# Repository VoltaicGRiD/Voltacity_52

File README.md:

## Voltacity

A custom designed, split ergonomic keyboard with 52 keys, designed for personal use. This repository contains the KiCAD files for the baseboard of the keyboard.

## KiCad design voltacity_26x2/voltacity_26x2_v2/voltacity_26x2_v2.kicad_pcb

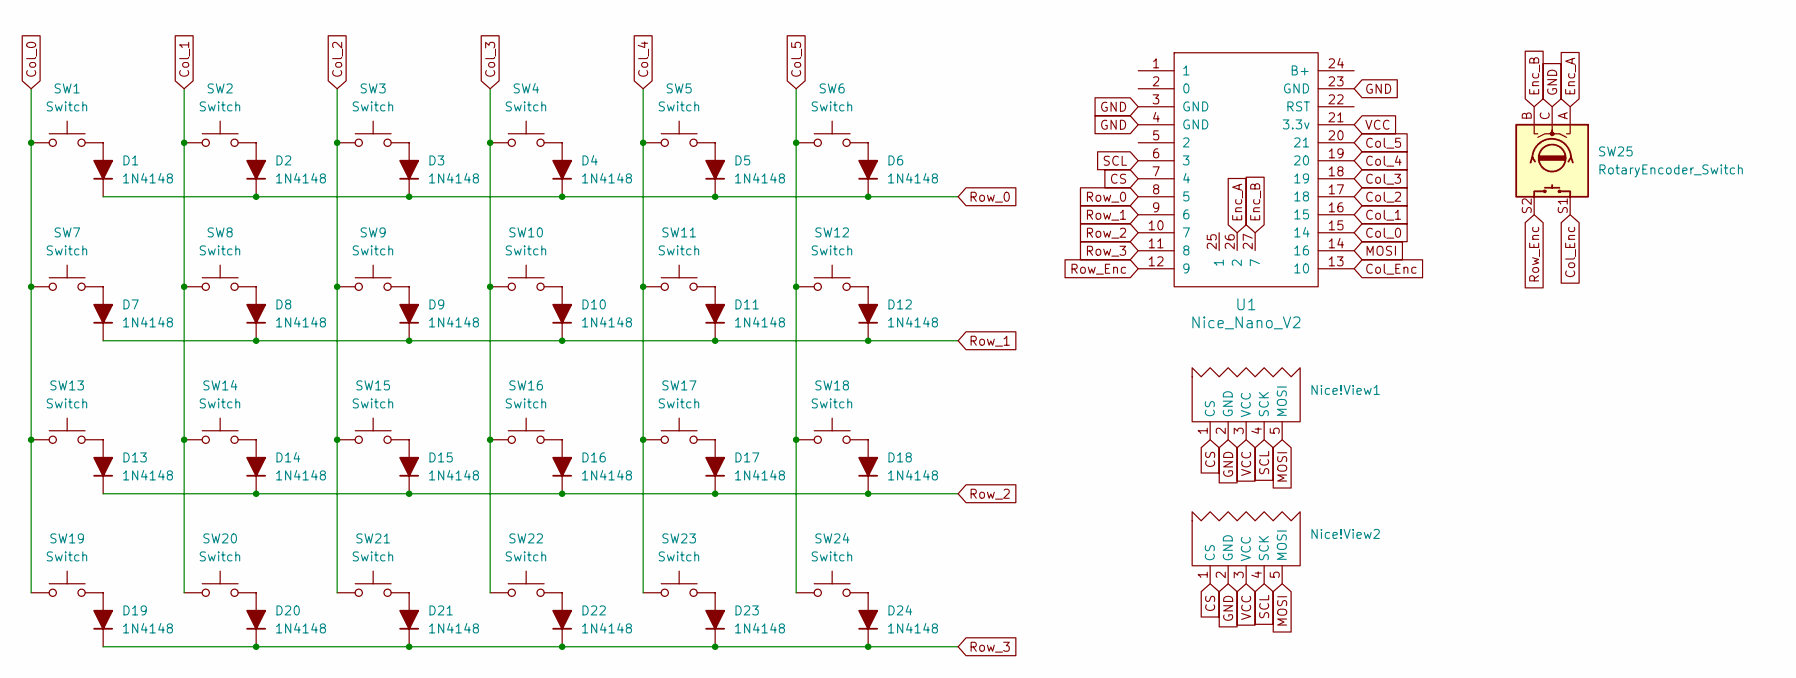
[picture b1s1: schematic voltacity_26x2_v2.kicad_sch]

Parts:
D1, D2, D3, D4, D5, D6, D7, D8, D9, D10, D11, D12, D13, D14, D15, D16, D17, D18, D19, D20, D21, D22, D23, D24: 1N4148; SOD123_DIO
Nice!View1, Nice!View2: Nice!View
SW1, SW2, SW3, SW4, SW5, SW6, SW7, SW8, SW9, SW10, SW11, SW12, SW13, SW14, SW15, SW16, SW17, SW18, SW19, SW20, SW21, SW22, SW23, SW24: Switch; SW_choc_Reversible_1u
SW25: RotaryEncoder_Switch; RotaryEncoder_Alps_EC11E-Switch_Vertical_H20mm_CircularMoun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
U1: Nice_Nano_V2

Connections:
CS: Nice!View1.1 (CS), Nice!View2.1 (CS), U1.7 (4); also elsewhere on the board
Col_0: SW1.1, SW7.1, SW13.1, SW19.1, U1.15 (14)
Col_1: SW2.1, SW8.1, SW14.1, SW20.1, U1.16 (15)
Col_2: SW3.1, SW9.1, SW15.1, SW21.1, U1.17 (18)
Col_3: SW4.1, SW10.1, SW16.1, SW22.1, U1.18 (19)
Col_4: SW5.1, SW11.1, SW17.1, SW23.1, U1.19 (20)
Col_5: SW6.1, SW12.1, SW18.1, SW24.1, U1.20 (21)
Col_Enc: SW25.S1, U1.13 (10)
Enc_A: SW25.A, U1.26 (2)
Enc_B: SW25.B, U1.27 (7)
GND: Nice!View1.2 (GND), Nice!View2.2 (GND), SW25.C, U1.3 (GND), U1.4 (GND), U1.23 (GND); also elsewhere on the board
MOSI: Nice!View1.5 (MOSI), Nice!View2.5 (MOSI), U1.14 (16); also elsewhere on the board
unnamed: D1.2 (A), SW1.2
unnamed: D2.2 (A), SW2.2
unnamed: D3.2 (A), SW3.2
unnamed: D4.2 (A), SW4.2
unnamed: D5.2 (A), SW5.2
unnamed: D6.2 (A), SW6.2
unnamed: D7.2 (A), SW7.2
unnamed: D8.2 (A), SW8.2
unnamed: D9.2 (A), SW9.2
unnamed: D10.2 (A), SW10.2
unnamed: D11.2 (A), SW11.2
unnamed: D12.2 (A), SW12.2
unnamed: D13.2 (A), SW13.2
unnamed: D14.2 (A), SW14.2
unnamed: D15.2 (A), SW15.2
unnamed: D16.2 (A), SW16.2
unnamed: D17.2 (A), SW17.2
unnamed: D18.2 (A), SW18.2
unnamed: D19.2 (A), SW19.2
unnamed: D20.2 (A), SW20.2
unnamed: D21.2 (A), SW21.2
unnamed: D22.2 (A), SW22.2
unnamed: D23.2 (A), SW23.2
unnamed: D24.2 (A), SW24.2
Row_0: D1.1 (K), D2.1 (K), D3.1 (K), D4.1 (K), D5.1 (K), D6.1 (K), U1.8 (5)
Row_1: D7.1 (K), D8.1 (K), D9.1 (K), D10.1 (K), D11.1 (K), D12.1 (K), U1.9 (6)
Row_2: D13.1 (K), D14.1 (K), D15.1 (K), D16.1 (K), D17.1 (K), D18.1 (K), U1.10 (7)
Row_3: D19.1 (K), D20.1 (K), D21.1 (K), D22.1 (K), D23.1 (K), D24.1 (K), U1.11 (8)
Row_Enc: SW25.S2, U1.12 (9)
SCL: Nice!View1.4 (SCK), Nice!View2.4 (SCK), U1.6 (3); also elsewhere on the board
VCC: Nice!View1.3 (VCC), Nice!View2.3 (VCC), U1.21 (3.3v); also elsewhere on the board

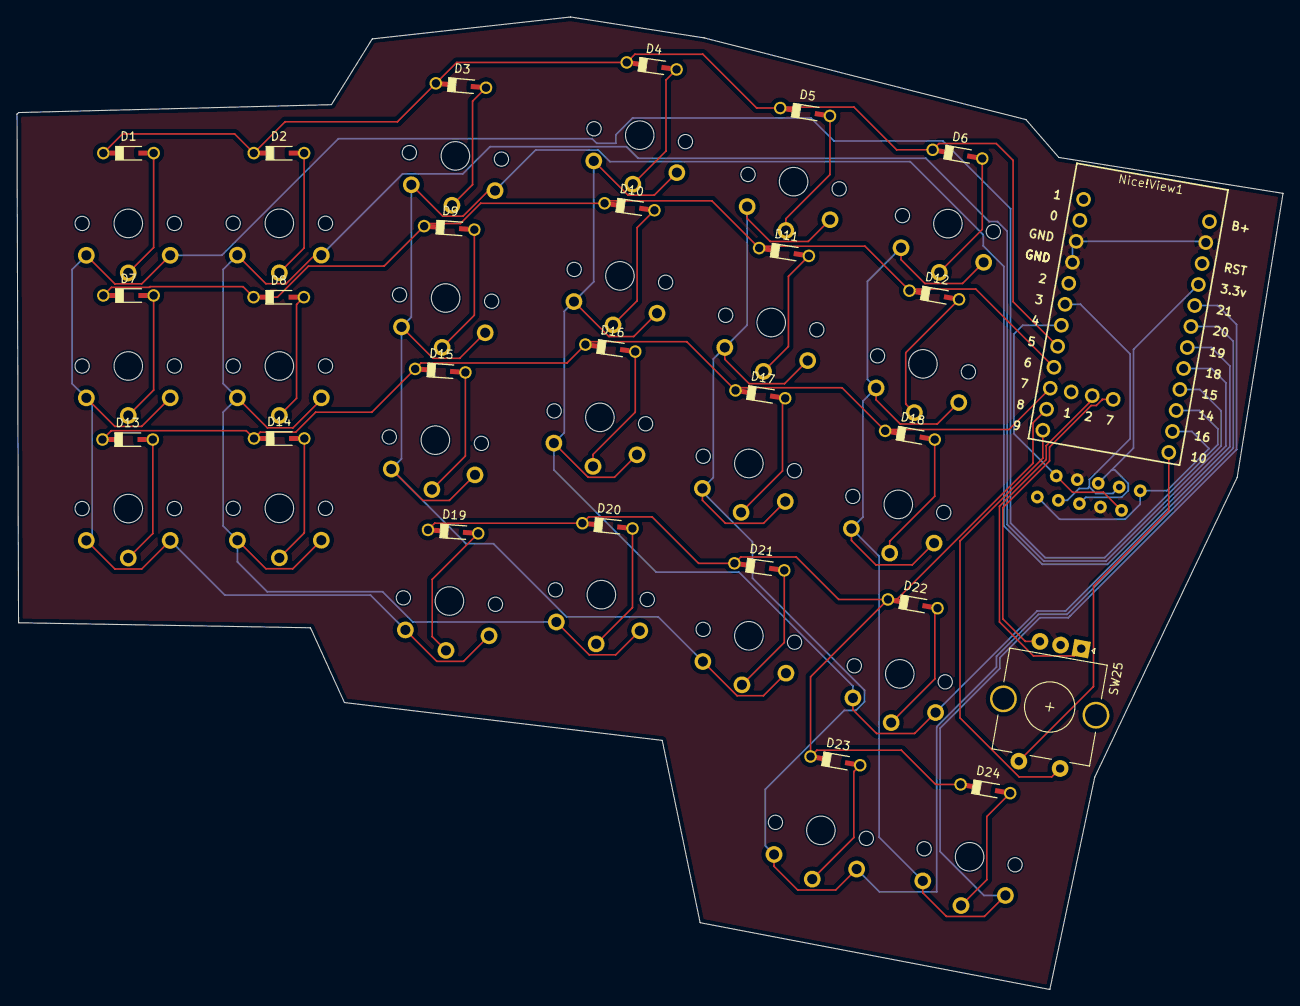
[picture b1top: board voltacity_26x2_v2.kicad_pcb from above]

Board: 2 copper layers, 150.9 x 115.9 mm, 52 parts (1 on the bottom side), 43 nets.

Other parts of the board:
Nice!View1#2: Nice!View

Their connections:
CS: Nice!View1#2.1 (CS); also elsewhere on the board
GND: Nice!View1#2.2 (GND); also elsewhere on the board
MOSI: Nice!View1#2.5 (MOSI); also elsewhere on the board
SCL: Nice!View1#2.4 (SCK); also elsewhere on the board
VCC: Nice!View1#2.3 (VCC); also elsewhere on the board

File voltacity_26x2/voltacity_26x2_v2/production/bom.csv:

Designator,Footprint,Quantity,Value,LCSC Part #
"D1, D10, D11, D12, D13, D14, D15, D16, D17, D18, D19, D2, D20, D21, D22, D23, D24, D3, D4, D5, D6, D7, D8, D9",SOD123_DIO,24,1N4148,
"SW1, SW10, SW11, SW12, SW13, SW14, SW15, SW16, SW17, SW18, SW19, SW2, SW20, SW21, SW22, SW23, SW24, SW3, SW4, SW5, SW6, SW7, SW8, SW9",SW_choc_Reversible_1u,24,Switch,
SW25,RotaryEncoder_Alps_EC11E-Switch_Vertical_H20mm_CircularMountingHoles,1,RotaryEncoder_Switch,
U1,Nice_Nano_V2,1,Nice_Nano_V2,

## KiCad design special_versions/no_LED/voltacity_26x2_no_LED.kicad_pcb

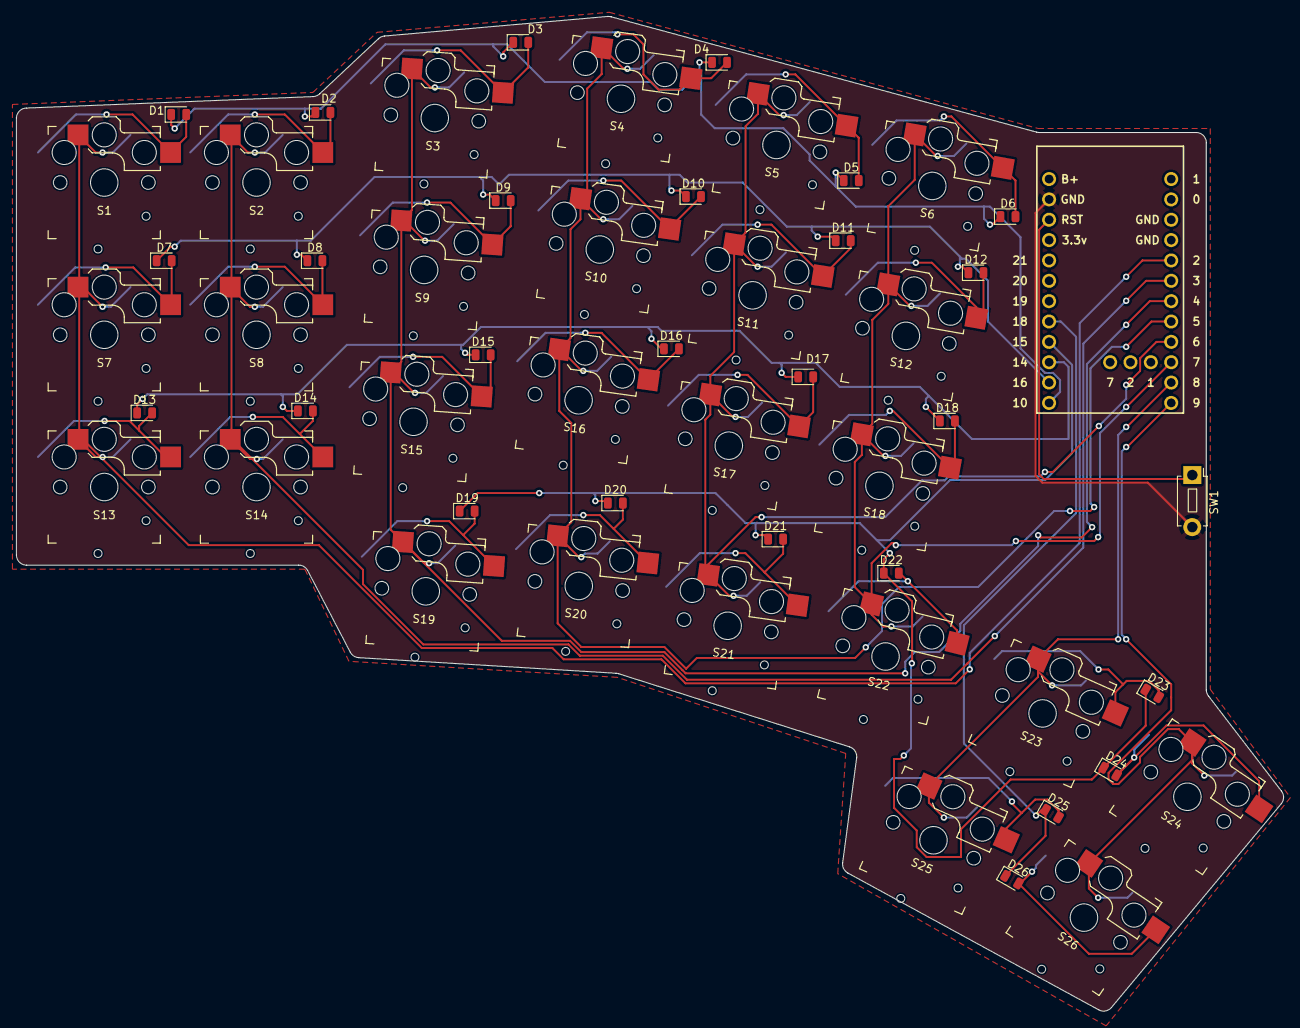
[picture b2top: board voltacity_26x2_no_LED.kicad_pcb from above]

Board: 2 copper layers, 158.1 x 124.1 mm, 54 parts (1 on the bottom side), 41 nets.

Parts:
D1, D2, D3, D4, D5, D6, D7, D8, D9, D10, D11, D12, D13, D14, D15, D16, D17, D18, D19, D20, D21, D22, D23, D24, D25, D26: Diode; D_0805_2012Metric
S1, S2, S3, S4, S5, S6, S7, S8, S9, S10, S11, S12, S13, S14, S15, S16, S17, S18, S19, S20, S21, S22, S23, S24, S25, S26: Keyswitch; REVERSED_Kailh_socket_PG1350_reversible
SW1: Switch; Button_MJTP1243
U1: Nice_Nano_V2

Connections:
Col_1: S1.1, S7.1, S13.1, U1.5 (2)
Col_2: S2.1, S8.1, S14.1, U1.6 (3)
Col_3: S3.1, S9.1, S15.1, S19.1, U1.7 (4)
Col_4: S4.1, S10.1, S16.1, S20.1, U1.8 (5)
Col_5: S5.1, S11.1, S17.1, S21.1, U1.9 (6)
Col_6: S6.1, S12.1, S18.1, S22.1, U1.10 (7)
Col_7: S23.1, S25.1, U1.11 (8)
Col_8: S24.1, S26.1, U1.12 (9)
GND: SW1.2, U1.23 (GND)
unnamed: D1.2 (A), S1.2
unnamed: D2.2 (A), S2.2
unnamed: D3.2 (A), S3.2
unnamed: D4.2 (A), S4.2
unnamed: D5.2 (A), S5.2
unnamed: D6.2 (A), S6.2
unnamed: D7.2 (A), S7.2
unnamed: D8.2 (A), S8.2
unnamed: D9.2 (A), S9.2
unnamed: D10.2 (A), S10.2
unnamed: D11.2 (A), S11.2
unnamed: D12.2 (A), S12.2
unnamed: D13.2 (A), S13.2
unnamed: D14.2 (A), S14.2
unnamed: D15.2 (A), S15.2
unnamed: D16.2 (A), S16.2
unnamed: D17.2 (A), S17.2
unnamed: D18.2 (A), S18.2
unnamed: D19.2 (A), S19.2
unnamed: D20.2 (A), S20.2
unnamed: D21.2 (A), S21.2
unnamed: D22.2 (A), S22.2
unnamed: D23.2 (A), S23.2
unnamed: D24.2 (A), S24.2
unnamed: D25.2 (A), S25.2
unnamed: D26.2 (A), S26.2
RESET: SW1.1, U1.22 (RST)
Row_1: D1.1 (K), D2.1 (K), D3.1 (K), D4.1 (K), D5.1 (K), D6.1 (K), U1.13 (10)
Row_2: D7.1 (K), D8.1 (K), D9.1 (K), D10.1 (K), D11.1 (K), D12.1 (K), U1.14 (16)
Row_3: D13.1 (K), D14.1 (K), D15.1 (K), D16.1 (K), D17.1 (K), D18.1 (K), U1.15 (14)
Row_4: D19.1 (K), D20.1 (K), D21.1 (K), D22.1 (K), D23.1 (K), D24.1 (K), U1.16 (15)
Row_5: D25.1 (K), D26.1 (K), U1.17 (18)

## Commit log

2024-07-07 Fixed the incorrect footprints for Kailh Choc hot-swap sockets
2024-07-07 Added new mounting holes
2024-07-11 Updated schematic and cleaned up some options
2024-07-14 Added .blend of case & plate
2024-07-14 Removed unneeded files
2024-07-14 Removed unneeded files #2
2024-07-26 Added v2
